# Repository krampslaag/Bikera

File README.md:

# Bikera
Turn bikes into IoT devices

What is Bikera? 
Bikera is a blockchain ecosystem that will function as a means to lend transportation and have it seamlessly maintained,
without having to worry about having a flat tire or any other mechanical difficulty that might cause inability to travel to your destination.

The Bikera network will always keep all the necessary parties informed on the latest and these will then swiftly present solutions. 
The means of transportation isn’t a solo challenge but a group effort. Depending on the class/group, roles will be assigned to accounts/persons. 
Acting on this role and delivering the requested solutions will result in a merit for these accounts/persons.

Accounts:
users would be comprised of classes/groups, each having a purpose to adding value to the ecosystem. Anyone can be in any or all of these groups. 

Consensus:
The ecosystem safeguarding will be done by the numbers of the masses and the randomness of travel-trajectory of these individuals,
this contributes to the Proof of Transit consensus protocol that will be used to mine the blocks.  
A layer2 solution will be used to track the bikes in movement; using LoraWAn nodes to verify the movement is real, 
this will route information to our own side blockchain, which will be used to fulfill contracts and token releases 
all our tokens will be created on this layer 2 or 1 blockchain for security reasons and immutability.  

Physical Assets:
Having real world assets used in a decentralized virtual system, needs a bridge between the virtual and the real world. 
This will be done by the development of a multi-functional lock. This lock will be implemented with a long-distance radio for receiving and transmitting data. 
There will also need to be storage to securely store private and public keys or other data. 
A GPS-module and/or Cellular network connectivity can be used to verify the location of the transportation, 
as feedback to the node network of gateway devices linking the lock to the blockchain. 

Wireless Communication: 
A network of radio receiving nodes need to be used or placed to receive data of these locks. 
Multiple nodes throughout a “two” dimensional space can be used to triangulate these locks and verify its location. 
The use-case of legacy or centralized networks can be used in the beginning and as verification of the decentralized network.

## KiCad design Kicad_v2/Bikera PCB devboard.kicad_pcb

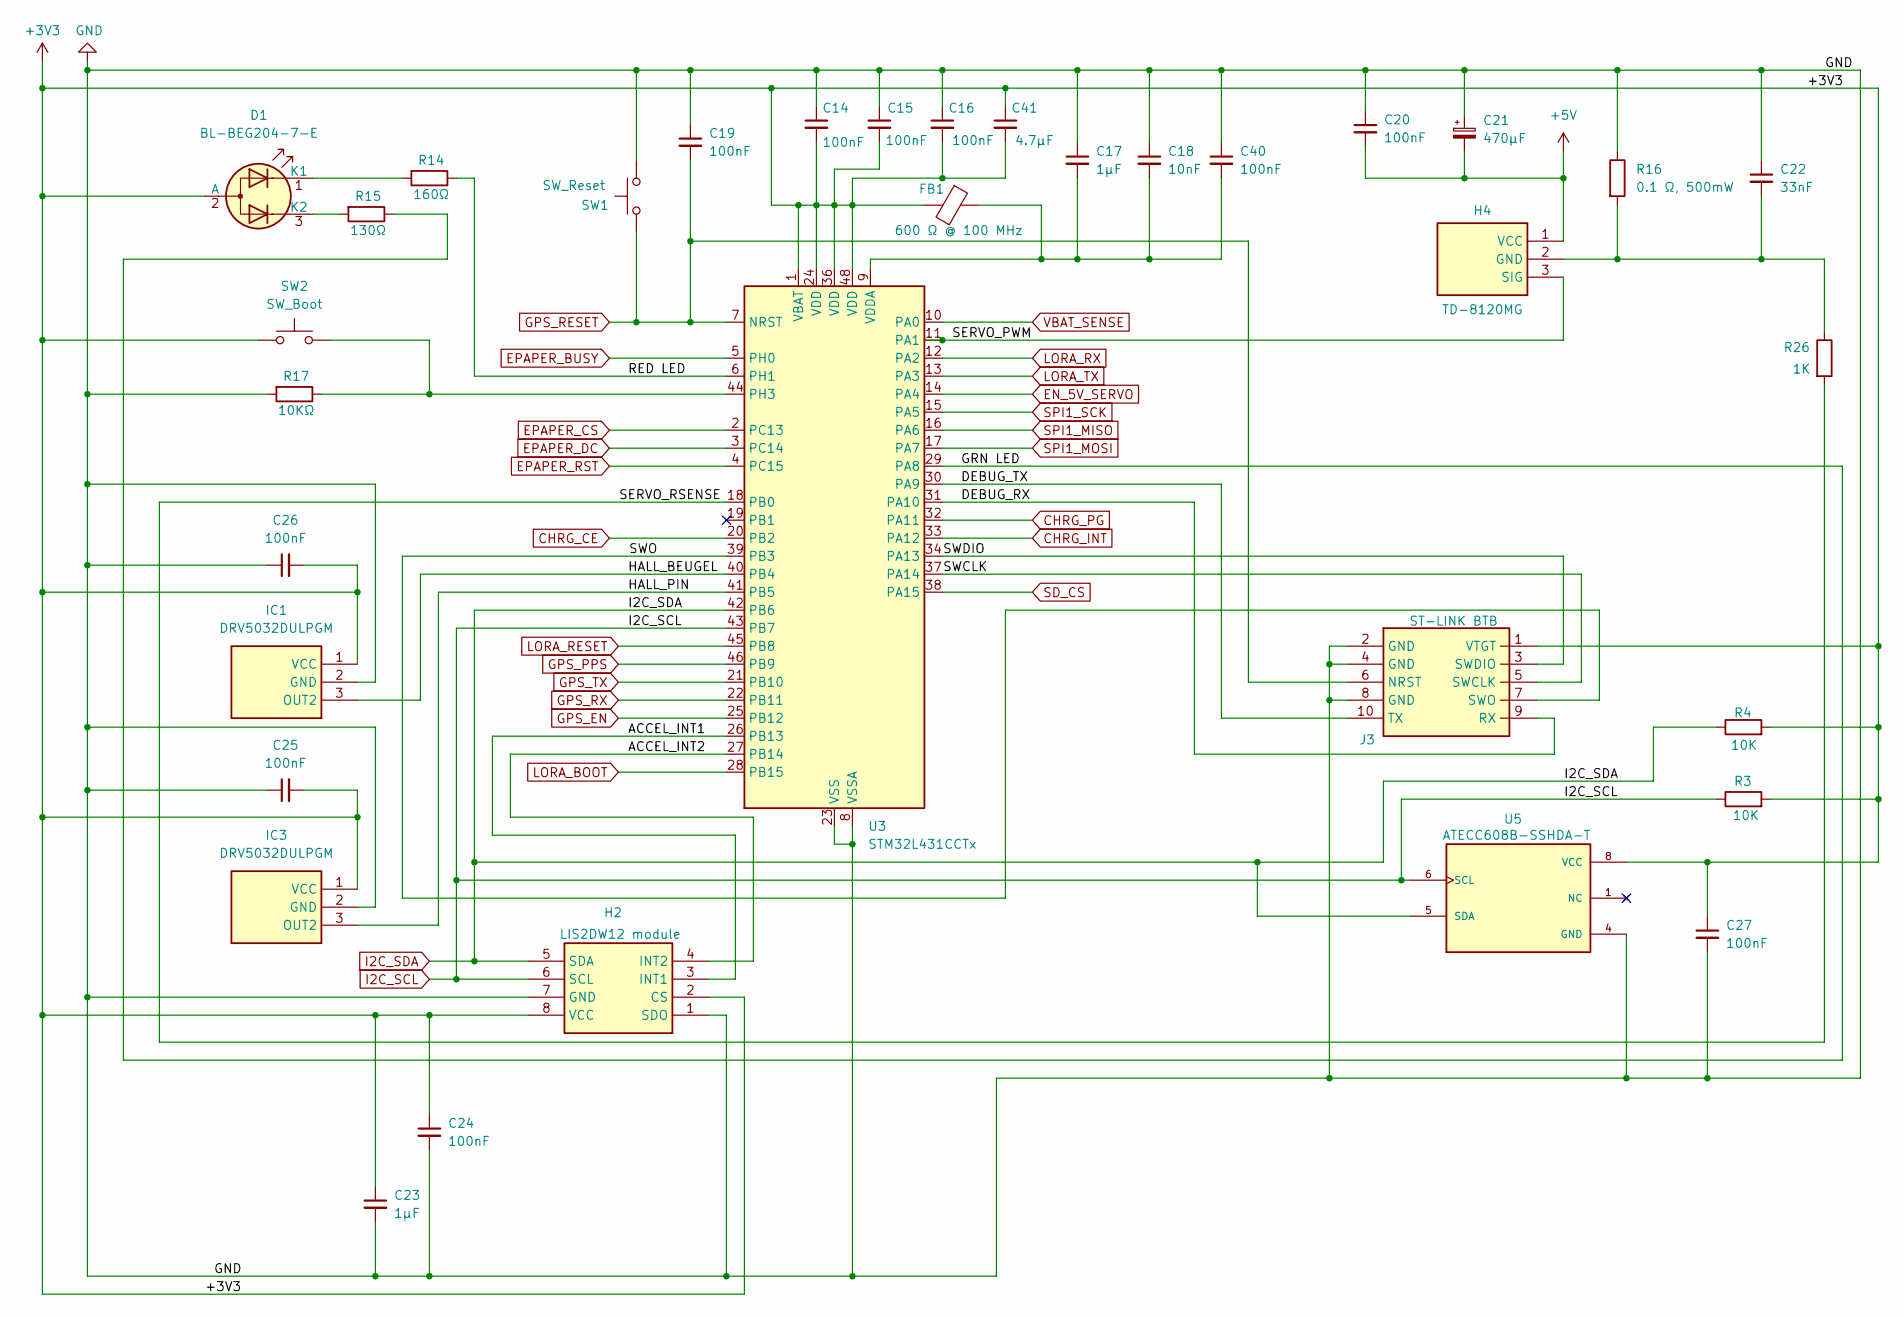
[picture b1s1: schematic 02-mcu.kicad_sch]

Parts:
C14, C15, C16, C19, C20, C24, C25, C26, C27, C40: 100nF; C_0603_1608Metric_Pad1.08x0.95mm_HandSolder
C17, C23: 1µF; C_0603_1608Metric_Pad1.08x0.95mm_HandSolder
C18: 10nF; C_0603_1608Metric_Pad1.08x0.95mm_HandSolder
C21: 470µF; CP_Radial_D8.0mm_P3.50mm
C22: 33nF; C_0603_1608Metric_Pad1.08x0.95mm_HandSolder
C41: 4.7µF; C_0603_1608Metric_Pad1.08x0.95mm_HandSolder
D1: BL-BEG204-7-E; LED_D5.0mm-3_Horizontal_O3.81mm_Z3.0mm
FB1: 600 Ω @ 100 MHz; L_0603_1608Metric_Pad1.05x0.95mm_HandSolder
H2: LIS2DW12 module; Mouser Part Number 727-FM24V01A-G
H4: TD-8120MG; JST_PH_B3B-PH-K_1x03_P2.00mm_Vertical; Mouser Part Number 595-DRV5032DULPGM
IC1, IC3: DRV5032DULPGM; Mouser Part Number 595-DRV5032DULPGM
J3: ST-LINK BTB; 009159010603906; Mouser Part Number 581-009159010603906
R3, R4: 10K; R_0603_1608Metric_Pad0.98x0.95mm_HandSolder
R14: 160Ω; R_0603_1608Metric_Pad0.98x0.95mm_HandSolder
R15: 130Ω; R_0603_1608Metric_Pad0.98x0.95mm_HandSolder
R16: 0.1 Ω, 500mW; R_1206_3216Metric_Pad1.30x1.75mm_HandSolder
R17: 10KΩ; R_0603_1608Metric_Pad0.98x0.95mm_HandSolder
R26: 1K; R_0603_1608Metric_Pad0.98x0.95mm_HandSolder
SW1: SW_Reset; SW_PUSH_6mm
SW2: SW_Boot; SW_PUSH_6mm
U3: STM32L431CCTx; LQFP-48_7x7mm_P0.5mm
U5: ATECC608B-SSHDA-T; DIP-8_W7.62mm_Socket; PARTREV B

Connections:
+3V3: C14.2, C15.2, C16.2, C23.1, C24.1, C25.2, C26.2, C27.1, C41.1, C41.2, D1.2 (A), FB1.2, H2.2 (CS), H2.8 (VCC), IC1.1 (VCC), IC3.1 (VCC), J3.1 (VTGT), R3.2, R4.2, SW2.1, U3.1 (VBAT), U3.24 (VDD), U3.36 (VDD), U3.48 (VDD), U5.8 (VCC); also elsewhere on the board
/MCU - Sensors - Actuators/ACCEL_INT1: H2.3 (INT1), U3.26 (PB13)
/MCU - Sensors - Actuators/ACCEL_INT2: H2.4 (INT2), U3.27 (PB14)
/MCU - Sensors - Actuators/DEBUG_RX: J3.9 (RX), U3.31 (PA10)
/MCU - Sensors - Actuators/DEBUG_TX: J3.10 (TX), U3.30 (PA9)
/MCU - Sensors - Actuators/GRN LED: R15.1, U3.29 (PA8)
/MCU - Sensors - Actuators/HALL_BEUGEL: IC1.3 (OUT2), U3.40 (PB4)
/MCU - Sensors - Actuators/HALL_PIN: IC3.3 (OUT2), U3.41 (PB5)
/MCU - Sensors - Actuators/RED LED: R14.1, U3.6 (PH1)
/MCU - Sensors - Actuators/SERVO_PWM: H4.3 (SIG), U3.11 (PA1)
/MCU - Sensors - Actuators/SERVO_RSENSE: R26.2, U3.18 (PB0)
/MCU - Sensors - Actuators/SWCLK: J3.5 (SWCLK), U3.37 (PA14)
/MCU - Sensors - Actuators/SWDIO: J3.3 (SWDIO), U3.34 (PA13)
/MCU - Sensors - Actuators/SWO: J3.7 (SWO), U3.39 (PB3)
CHRG_CE: U3.20 (PB2); also elsewhere on the board
CHRG_INT: U3.33 (PA12); also elsewhere on the board
CHRG_PG: U3.32 (PA11); also elsewhere on the board
EN_5V_SERVO: U3.14 (PA4); also elsewhere on the board
EPAPER_BUSY: U3.5 (PH0); also elsewhere on the board
EPAPER_CS: U3.2 (PC13); also elsewhere on the board
EPAPER_DC: U3.3 (PC14); also elsewhere on the board
EPAPER_RST: U3.4 (PC15); also elsewhere on the board
GND: C14.1, C15.1, C16.1, C17.1, C18.1, C19.1, C20.1, C21.1, C22.1, C23.2, C24.2, C25.1, C26.1, C27.2, C40.1, H2.1 (SDO), H2.7 (GND), IC1.2 (GND), IC3.2 (GND), J3.2 (GND), J3.4 (GND), J3.8 (GND), R16.1, R17.2, SW1.2, U3.8 (VSSA), U3.23 (VSS), U3.35 (VSS), U3.47 (VSS), U5.4 (GND); also elsewhere on the board
GPS_EN: U3.25 (PB12); also elsewhere on the board
GPS_PPS: U3.46 (PB9); also elsewhere on the board
GPS_RESET: C19.2, J3.6 (NRST), SW1.1, U3.7 (NRST); also elsewhere on the board
GPS_RX: U3.22 (PB11); also elsewhere on the board
GPS_TX: U3.21 (PB10); also elsewhere on the board
I2C_SCL: H2.6 (SCL), R3.1, U3.43 (PB7), U5.6 (SCL); also elsewhere on the board
I2C_SDA: H2.5 (SDA), R4.1, U3.42 (PB6), U5.5 (SDA); also elsewhere on the board
LORA_BOOT: U3.28 (PB15); also elsewhere on the board
LORA_RESET: U3.45 (PB8); also elsewhere on the board
LORA_RX: U3.12 (PA2); also elsewhere on the board
LORA_TX: U3.13 (PA3); also elsewhere on the board
unnamed: D1.1 (K1), R14.2
unnamed: D1.3 (K2), R15.2
unnamed: C22.2, H4.2 (GND), R16.2, R26.1
unnamed: R17.1, SW2.2, U3.44 (PH3)
unnamed: C17.2, C18.2, C40.2, FB1.1, U3.9 (VDDA)
SD_CS: U3.38 (PA15); also elsewhere on the board
SPI1_MISO: U3.16 (PA6); also elsewhere on the board
SPI1_MOSI: U3.17 (PA7); also elsewhere on the board
SPI1_SCK: U3.15 (PA5); also elsewhere on the board
VBAT_SENSE: U3.10 (PA0); also elsewhere on the board

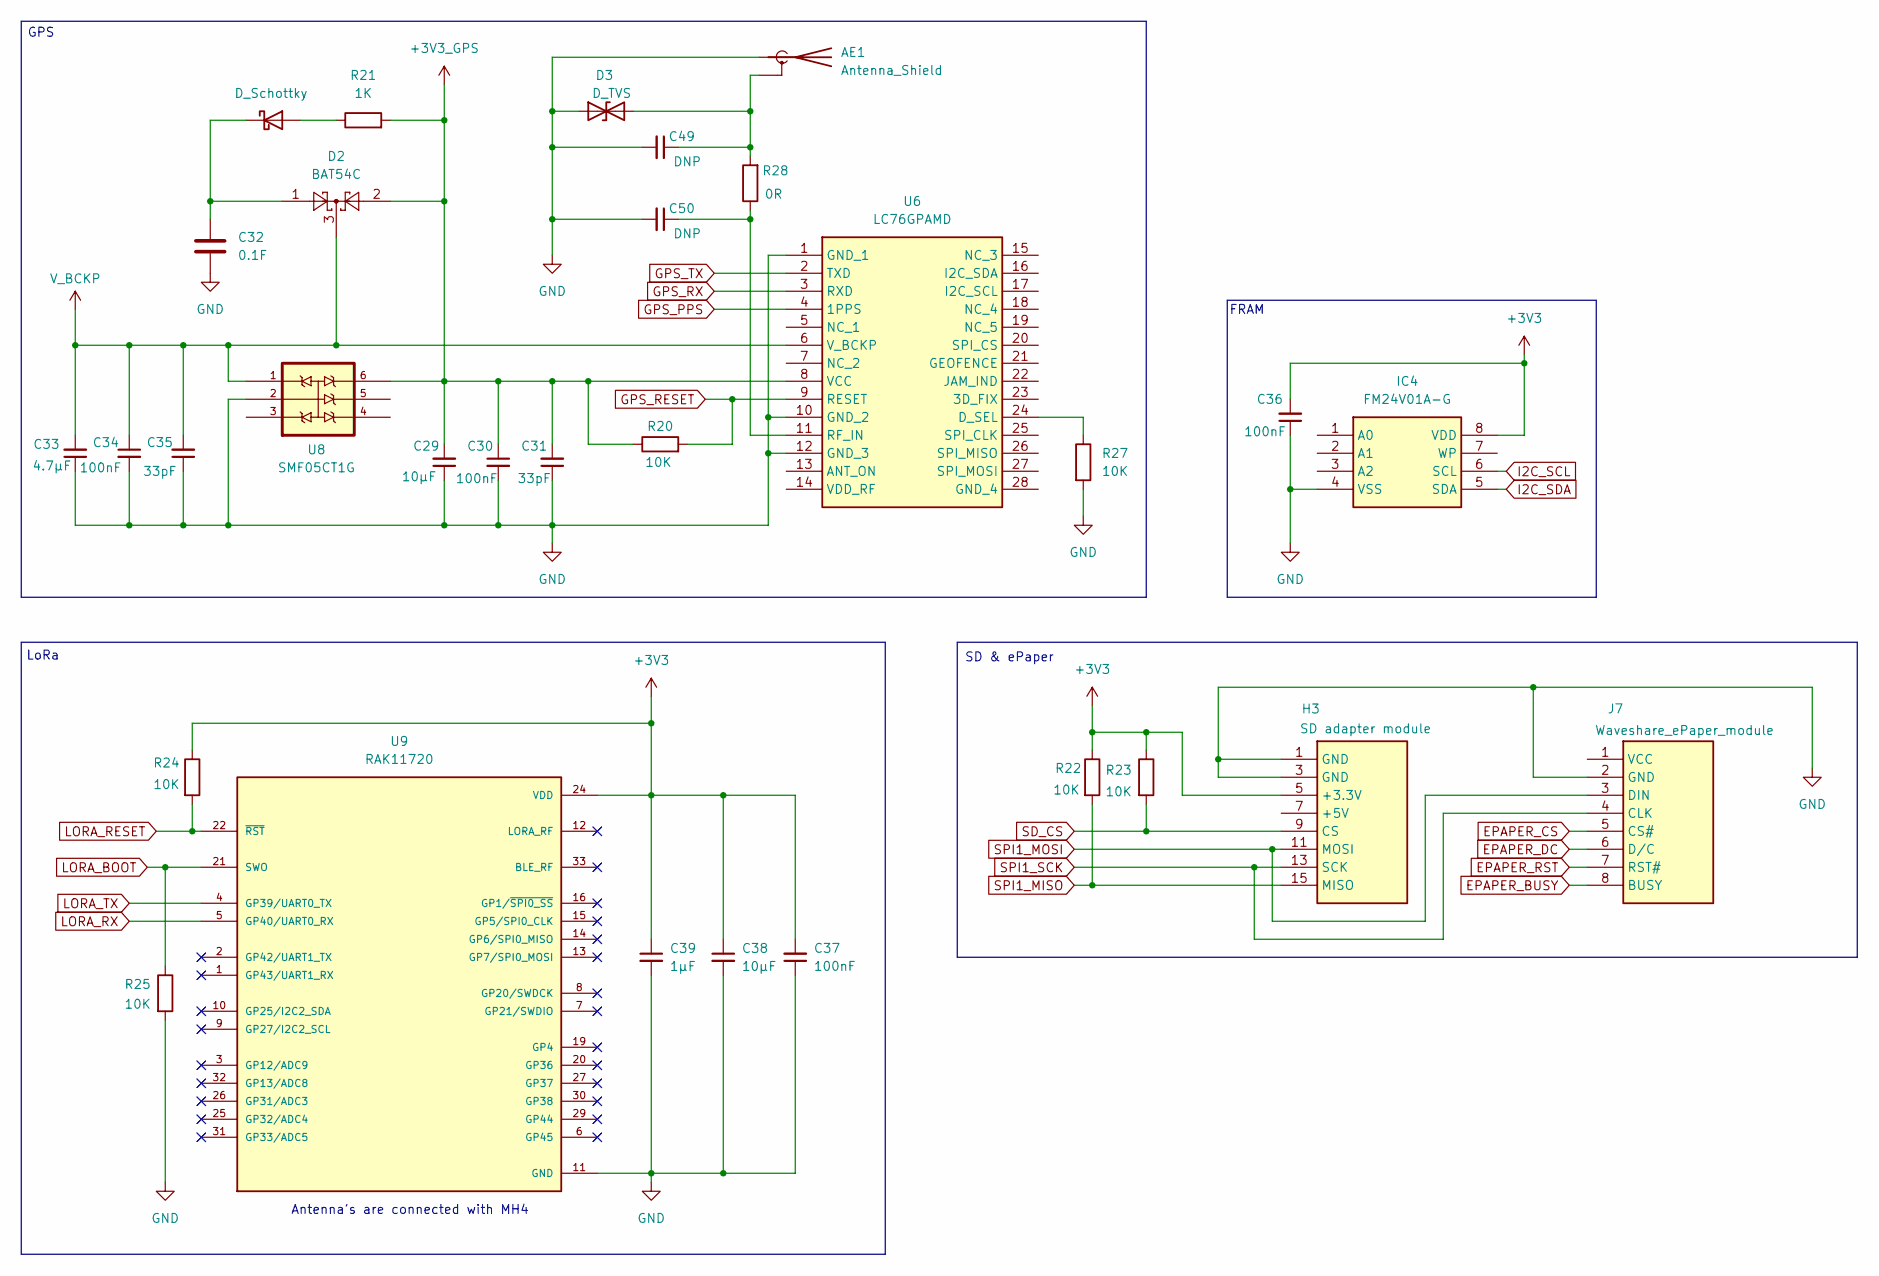
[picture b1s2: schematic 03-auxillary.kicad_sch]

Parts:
AE1: Antenna_Shield; U.FL_Hirose_U.FL-R-SMT-1_Vertical
C29, C38: 10µF; C_0603_1608Metric_Pad1.08x0.95mm_HandSolder
C30, C34, C36, C37: 100nF; C_0603_1608Metric_Pad1.08x0.95mm_HandSolder
C31, C35: 33pF; C_0603_1608Metric_Pad1.08x0.95mm_HandSolder
C32: 0.1F; C_1210_3225Metric_Pad1.33x2.70mm_HandSolder
C33: 4.7µF; C_0603_1608Metric_Pad1.08x0.95mm_HandSolder
C39: 1µF; C_0603_1608Metric_Pad1.08x0.95mm_HandSolder
C49, C50: DNP; C_0402_1005Metric_Pad0.74x0.62mm_HandSolder
D2: BAT54C; SOT-23_Handsoldering
D3: D_TVS; D_SOD-923
D4: D_Schottky; D_SOD-523
H3: SD adapter module; PinHeader_2x08_P2.54mm_Vertical
IC4: FM24V01A-G; SOIC127P602X173-8N; Mouser Part Number 727-FM24V01A-G
J7: Waveshare_ePaper_module; JST_PH_B8B-PH-K_1x08_P2.00mm_Vertical
R20, R22, R23, R24, R25, R27: 10K; R_0603_1608Metric_Pad0.98x0.95mm_HandSolder
R21: 1K; R_0603_1608Metric_Pad0.98x0.95mm_HandSolder
R28: 0R; R_0402_1005Metric_Pad0.72x0.64mm_HandSolder
U6: LC76GPAMD; Mouser Part Number 277-LC76GPAMD
U8: SMF05CT1G; SOT65P210X110-6N
U9: RAK11720; XCVR_RAK11720; PARTREV 6/2/2023

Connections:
+3V3: C36.2, C37.2, C38.1, C39.1, H3.5 (+3.3V), H3.6 (+3.3V), IC4.8 (VDD), R22.1, R23.1, R24.1, U9.24 (VDD); also elsewhere on the board
+3V3_GPS: C29.2, C30.1, C31.2, D2.2, R20.1, R21.2, U6.8 (VCC), U8.6; also elsewhere on the board
EPAPER_BUSY: J7.8 (BUSY); also elsewhere on the board
EPAPER_CS: J7.5 (CS#); also elsewhere on the board
EPAPER_DC: J7.6 (D/C); also elsewhere on the board
EPAPER_RST: J7.7 (RST#); also elsewhere on the board
GND: AE1.1 (A), C29.1, C30.2, C31.1, C32.2, C33.1, C34.2, C35.1, C36.1, C37.1, C38.2, C39.2, C49.2, C50.2, D3.1 (A1), H3.1 (GND), H3.2 (GND), H3.3 (GND), H3.4 (GND), IC4.4 (VSS), J7.2 (GND), R25.2, R27.2, U6.1 (GND_1), U6.10 (GND_2), U6.12 (GND_3), U8.2, U9.11 (GND), U9.17 (GND), U9.18 (GND), U9.23 (GND), U9.28 (GND), U9.34 (GND); also elsewhere on the board
GPS_PPS: U6.4 (1PPS); also elsewhere on the board
GPS_RESET: R20.2, U6.9 (RESET); also elsewhere on the board
GPS_RX: U6.3 (RXD); also elsewhere on the board
GPS_TX: U6.2 (TXD); also elsewhere on the board
I2C_SCL: IC4.6 (SCL); also elsewhere on the board
I2C_SDA: IC4.5 (SDA); also elsewhere on the board
LORA_BOOT: R25.1, U9.21 (SWO); also elsewhere on the board
LORA_RESET: R24.2, U9.22 (~RST); also elsewhere on the board
LORA_RX: U9.5 (GP40/UART0_RX); also elsewhere on the board
LORA_TX: U9.4 (GP39/UART0_TX); also elsewhere on the board
unnamed: AE1.2 (Shield), C49.1, D3.2 (A2), R28.2
unnamed: D4.2 (A), R21.1
unnamed: C32.1, D2.1, D4.1 (K)
unnamed: R27.1, U6.24 (D_SEL)
unnamed: C50.1, R28.1, U6.11 (RF_IN)
SD_CS: H3.9 (CS), H3.10 (CS), R23.2; also elsewhere on the board
SPI1_MISO: H3.15 (MISO), H3.16 (MISO), R22.2; also elsewhere on the board
SPI1_MOSI: H3.11 (MOSI), H3.12 (MOSI), J7.3 (DIN); also elsewhere on the board
SPI1_SCK: H3.13 (SCK), H3.14 (SCK), J7.4 (CLK); also elsewhere on the board
V_BCKP: C33.2, C34.1, C35.2, D2.3, U6.6 (V_BCKP), U8.1

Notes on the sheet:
Antenna's are connected with MH4
LoRa
SD & ePaper
GPS
FRAM

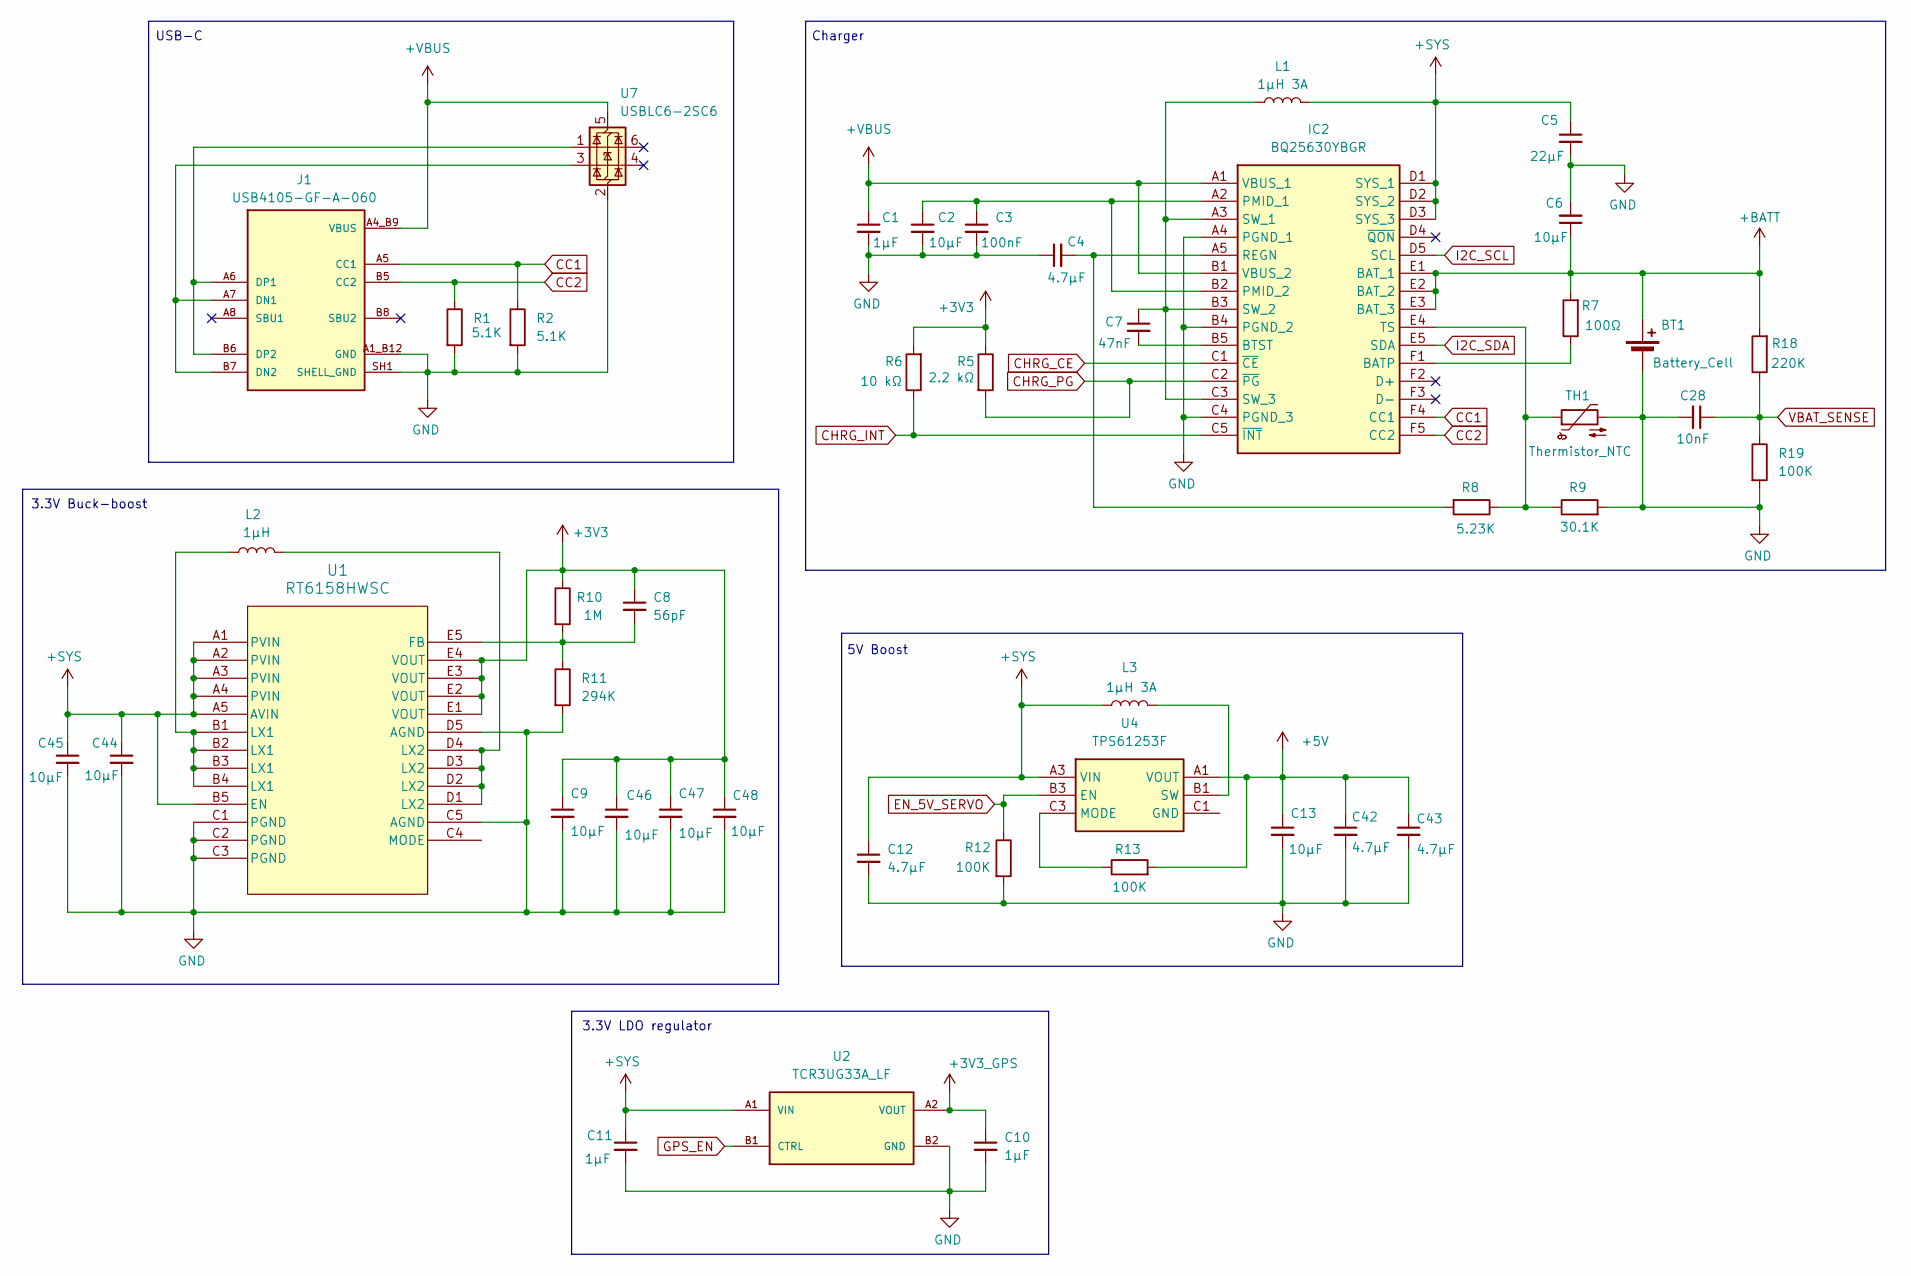
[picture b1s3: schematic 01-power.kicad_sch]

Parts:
BT1: Battery_Cell; JST_PH_S2B-PH-K_1x02_P2.00mm_Horizontal
C1, C10, C11: 1µF; C_0603_1608Metric_Pad1.08x0.95mm_HandSolder
C2, C6, C9, C13, C44, C45, C46, C47, C48: 10µF; C_0603_1608Metric_Pad1.08x0.95mm_HandSolder
C3: 100nF; C_0603_1608Metric_Pad1.08x0.95mm_HandSolder
C4, C12, C42, C43: 4.7µF; C_0603_1608Metric_Pad1.08x0.95mm_HandSolder
C5: 22µF; C_0805_2012Metric_Pad1.18x1.45mm_HandSolder
C7: 47nF; C_0603_1608Metric_Pad1.08x0.95mm_HandSolder
C8: 56pF; C_0603_1608Metric_Pad1.08x0.95mm_HandSolder
C28: 10nF; C_0603_1608Metric_Pad1.08x0.95mm_HandSolder
IC2: BQ25630YBGR; BGA30C40P5X6_221X271X50; Manufacturer_Part_Number BQ25630YBGR
J1: USB4105-GF-A-060; USB_C_Receptacle_GCT_USB4105-xx-A_16P_TopMnt_Horizontal
L1, L3: 1µH 3A; MAKK2520H1R0M
L2: 1µH; MAKK2520H1R0M
R1, R2: 5.1K; R_0603_1608Metric_Pad0.98x0.95mm_HandSolder
R5: 2.2 kΩ; R_0603_1608Metric_Pad0.98x0.95mm_HandSolder
R6: 10 kΩ; R_0603_1608Metric_Pad0.98x0.95mm_HandSolder
R7: 100Ω; R_0603_1608Metric_Pad0.98x0.95mm_HandSolder
R8: 5.23K; R_0603_1608Metric_Pad0.98x0.95mm_HandSolder
R9: 30.1K; R_0603_1608Metric_Pad0.98x0.95mm_HandSolder
R10: 1M; R_0402_1005Metric
R11: 294K; R_0402_1005Metric
R12, R13, R19: 100K; R_0603_1608Metric_Pad0.98x0.95mm_HandSolder
R18: 220K; R_0603_1608Metric_Pad0.98x0.95mm_HandSolder
TH1: Thermistor_NTC; C_Disc_D3.4mm_W2.1mm_P2.50mm
U1: RT6158HWSC; BGA25_RT6158H_RIT-M
U2: TCR3UG33A_LF; BGA4N35P2X2_64X64X33; PARTREV 2021-10-28
U4: TPS61253F; BGA9N40P3X3_119X128X62N; Mouser Part Number 727-FM24V01A-G
U7: USBLC6-2SC6; SOT-23-6_Handsoldering

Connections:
+3V3: C8.1, C9.1, C46.1, C47.1, C48.1, R5.1, R6.2, R10.1, U1.E1 (VOUT), U1.E2 (VOUT), U1.E3 (VOUT), U1.E4 (VOUT); also elsewhere on the board
+3V3_GPS: C10.1, U2.A2 (VOUT); also elsewhere on the board
+BATT: BT1.1 (+), C6.1, IC2.E1 (BAT_1), IC2.E2 (BAT_2), IC2.E3 (BAT_3), R7.2, R18.2
+SYS: C5.1, C11.1, C12.1, C44.1, C45.1, IC2.D1 (SYS_1), IC2.D2 (SYS_2), IC2.D3 (SYS_3), L1.2, L3.1, U1.A1 (PVIN), U1.A2 (PVIN), U1.A3 (PVIN), U1.A4 (PVIN), U1.A5 (AVIN), U1.B5 (EN), U2.A1 (VIN), U4.A3 (VIN)
+VBUS: C1.1, IC2.A1 (VBUS_1), IC2.B1 (VBUS_2), J1.A4_B9 (VBUS), J1.B4_A9 (VBUS), U7.5 (VBUS)
CC1: IC2.F4 (CC1), J1.A5 (CC1), R2.1
CC2: IC2.F5 (CC2), J1.B5 (CC2), R1.1
CHRG_CE: IC2.C1 (~CE); also elsewhere on the board
CHRG_INT: IC2.C5 (~INT), R6.1; also elsewhere on the board
CHRG_PG: IC2.C2 (~PG), R5.2; also elsewhere on the board
EN_5V_SERVO: R12.1, U4.B3 (EN); also elsewhere on the board
GND: BT1.2 (-), C1.2, C2.2, C3.2, C4.1, C5.2, C6.2, C9.2, C10.2, C11.2, C12.2, C13.2, C28.2, C42.2, C43.2, C44.2, C45.2, C46.2, C47.2, C48.2, IC2.A4 (PGND_1), IC2.B4 (PGND_2), IC2.C4 (PGND_3), J1.A1_B12 (GND), J1.B1_A12 (GND), J1.SH1 (SHELL_GND), J1.SH2 (SHELL_GND), J1.SH3 (SHELL_GND), J1.SH4 (SHELL_GND), R1.2, R2.2, R9.2, R11.2, R12.2, R19.2, TH1.2, U1.C1 (PGND), U1.C2 (PGND), U1.C3 (PGND), U1.C5 (AGND), U1.D5 (AGND), U2.B2 (GND), U7.2 (GND); also elsewhere on the board
GPS_EN: U2.B1 (CTRL); also elsewhere on the board
I2C_SCL: IC2.D5 (SCL); also elsewhere on the board
I2C_SDA: IC2.E5 (SDA); also elsewhere on the board
unnamed: IC2.F1 (BATP), R7.1
unnamed: C7.2, IC2.B5 (BTST)
unnamed: C2.1, C3.1, IC2.A2 (PMID_1), IC2.B2 (PMID_2)
unnamed: C4.2, IC2.A5 (REGN), R8.2
unnamed: C7.1, IC2.A3 (SW_1), IC2.B3 (SW_2), IC2.C3 (SW_3), L1.1
unnamed: IC2.E4 (TS), R8.1, R9.1, TH1.1
unnamed: J1.A7 (DN1), J1.B7 (DN2), U7.3 (I/O2)
unnamed: J1.A6 (DP1), J1.B6 (DP2), U7.1 (I/O1)
unnamed: L2.1, U1.B1 (LX1), U1.B2 (LX1), U1.B3 (LX1), U1.B4 (LX1)
unnamed: L2.2, U1.D1 (LX2), U1.D2 (LX2), U1.D3 (LX2), U1.D4 (LX2)
unnamed: L3.2, U4.B1 (SW), U4.B2 (SW)
unnamed: C8.2, R10.2, R11.1, U1.E5 (FB)
unnamed: U4.C1 (GND), U4.C2 (GND)
unnamed: R13.1, U4.C3 (MODE)
VBAT_SENSE: C28.1, R18.1, R19.1; also elsewhere on the board

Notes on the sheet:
3.3V Buck-boost
USB-C
3.3V LDO regulator
5V Boost
Charger

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
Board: 4 copper layers, 114 parts (48 on the bottom side), 71 nets, no tracks yet.

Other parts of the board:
H10, H11, H12, H13: MountingHole_3.2mm_M3_Pad

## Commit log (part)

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2023-08-08 white paper for the Bikera Network
2023-08-08 MERA logo
2023-08-08 Create README.md
    Short description of the Bikera network
2023-08-08 The whitepaper for the Bikera network
2024-02-25 bikera v2.1
    smart contract for audit purposess
2024-02-25 Bikera Smart contract V1
    audit purposes, old version contract
2024-02-25 version 2.1
    finalised version for token launch, tested on sepolia network
    see on sepolia etherscan
    contract adress:
    0x25EE85C5E86293C8Ba874A505F4C5D21c19231F9
2024-03-08 new logo for Bikera MERA
2024-03-08 Deployed contract on Ethereum
2024-10-03 mkdir my-new-folder
2024-10-04 Update Helium_integration_v0.0.1.json
    trying to get array input HEX as array output HEX, so that in further programs the conversion is in INT of HEX format. this to save data on blockchain, find out which data size runs natively and fast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
2024-10-04 Update Helium_integration_v0.0.1.json
    got HEX output, INT output and String output, compatibility arr.
2024-10-04 Update Helium_integration_v0.0.1.json
    HEX (16) Integer (10) !! Base64 needs or can be added if necessary.
2024-10-07 Update MKRWAN_PAYLOAD_CUSTOM_BIKERA.ino
    Trying to get it functioning with the Wio module for gps coordinates.
2024-10-07 Update and rename Helium_integration_v0.0.1.json to Helium_integration_v0.0.1.js
    Is written in javascript. Not sure if json or nodjs extension should be required. Get Helium CLI and find out!
2024-10-14 Update MKRWAN_PAYLOAD_CUSTOM_BIKERA.ino
    big lines of draft of draft of draft of draft of DRAFT
2024-10-15 Update MKRWAN_PAYLOAD_CUSTOM_BIKERA.ino
    starting connection en setting up lock partially structure line-out
2024-10-15 Update MKRWAN_PAYLOAD_CUSTOM_BIKERA.ino
    workloads, private key generation or input added. And device check by calculating public key
2024-10-16 Update MKRWAN_PAYLOAD_CUSTOM_BIKERA.ino
    Crypto chip setup part, input private key (have a copy of the wallet address in case the chip dies or the lock gets destroyed the funds are still accessible by generating a mobile wallet with the key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
2024-10-16 Update MKRWAN_PAYLOAD_CUSTOM_BIKERA.ino
    some notably interesting info on how to use the ECC608 crypto key and future imlpications of the network
2024-10-18 Update MKRWAN_PAYLOAD_CUSTOM_BIKERA.ino
    LFG for this iteration, now just make the arduino send random numbers that should be locked as coordinates with assigned Public key encryption.
2024-10-20 Update MKRWAN_PAYLOAD_CUSTOM_BIKERA.ino
    Setup, entering stuff, probably should write this to EEPROM; in case somebody just start cracking open the locks and replaces SD-cards with malicious ones, depends on if the price of an SD card is wo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
2024-10-21 Update MKRWAN_PAYLOAD_CUSTOM_BIKERA.ino
    Let's try to compile this Gaint Bug of code
2024-10-21 Update MKRWAN_PAYLOAD_CUSTOM_BIKERA.ino
    Debuugggiiiinnnngggg
2024-10-23 Update MKRWAN_PAYLOAD_CUSTOM_BIKERA.ino
    debugged and compiles.
    let's take this for a testdrive. Next is head-on with the configuration file. this is now set to TLS but it is not completely similar on which slots to lock and which to use for this application
2024-10-23 Update MKRWAN_PAYLOAD_CUSTOM_BIKERA.ino
    Fixing bugs
2024-10-24 Update MKRWAN_PAYLOAD_CUSTOM_BIKERA.ino
    getting the setup to run, serial monitor conversion needs to be looked at. trying other desktop environment maybe this is due to Debian12 and the UART interface. let's see If this isn't a problem on 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
2024-10-25 Update MKRWAN_PAYLOAD_CUSTOM_BIKERA.ino
    flashstorage problems with strings.
2024-10-25 Rename MKRWAN_PAYLOAD_CUSTOM_BIKERA.ino to MKRWAN_PAYLOAD_CUSTOM_BIKERA_MKRWAN1310.ino
    this is the MKRWAN firmware prototype, later in development the Arduino NANO ble 33 IOT will also be used and after setting these two type boards up to run firmware for Bikera network ESP32 will be t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
2024-10-25 Update MKRWAN_PAYLOAD_CUSTOM_BIKERA_MKRWAN1310.ino
    trying to get the serial input to read bytes as hexadecimal format
2025-01-21 Create test file to create folder
2025-01-21 Create test
2025-07-02 Create PotBotBlock_Telegram
2025-08-14 telegram bot replit version
2025-08-14 Remove nested repository and add to gitignore
2025-08-15 Your commit message
2025-08-15 update 15082025e
2025-08-15 20250815d
2025-08-20 front end webpage online added correctly twice
2025-08-20 front end webpage added services
2025-08-23 Add Backend Components
2025-08-24 Powerpoint presentation
2025-08-25 Powerpoint presentation v2
2025-08-28 rust implementation of canisters on ICP
2025-08-28 rust implementation of canisters on ICP compartementalize
2025-08-28 Remove node_modules and add to gitignore
2025-08-28 Add dfx files to gitignore
2025-08-28 Add compressor and wrangler config
2025-08-31 got canisters working locally
2025-08-31 Remove build artifacts from version control
2025-08-31 Add .gitignore to exclude build artifacts
2025-08-31 cleaned up version
2025-08-31 failed copy paste
2025-08-31 getting te canisters to function in sync and get it running on mainnet ICP
2025-08-31 supabase and worker.js update monster, need XP canister stil debug and go
2025-08-31 final update today, XP token added and the API routes that need refining to link front to back
2025-09-07 added API routing and correcting variable naming
2025-09-14 architectural format of the canisters
2025-09-14 cleaning up a littles
2025-09-21 getting ready for regulations
2025-10-07 user database for ICP
2026-02-04 Document voor componenten, STM32L0, L1 en L4 vergeleken
2026-02-05 STM32 prijzen en voorstel
2026-02-05 STM32WL?
2026-02-06 LoRa
2026-02-11 LoRa antennes
2026-02-22 ECC chip: ATECC608B
2026-02-23 Draadantenne
2026-02-28 BLE antenne
2026-03-01 ECC update
2026-03-02 GPS u-blox
2026-03-03 GPS Quectel
2026-03-06 E-ink
2026-03-10 Accelerometer
2026-03-11 Readme
2026-03-16 Architectuur schema begin
2026-03-19 Architectuur schema
2026-03-20 Architectuurschema Lora, GPS, ePaper
2026-03-24 BMS lader en USB stromen
2026-03-26 BMS converters
2026-03-27 BMS 5V boost
2026-03-27 Inhoudstafel
2026-03-31 5V boost
2026-04-01 5V boost en accelerometer
2026-04-19 Kleurled en hall effect sensor
2026-04-21 Architectuurschema FRAM en accelerometer
2026-04-22 Architectuurschema BMS
2026-04-25 Architectuur schema structuur
2026-04-28 LED, GPS antenne
2026-04-29 Architectuurschema LED en GPS antenne
2026-04-29 Componenten bijgewerkt en architectuurschema hall sensors
2026-05-02 ST-link
2026-05-06 KiCad project aangemaakt
2026-05-06 untrack .history
2026-05-07 untrack backups
2026-05-07 KiCad symbolen geïmporteerd
2026-05-08 Readme makeover - stand van zaken
2026-05-08 Readme update
2026-05-12 KiCad symbolen basiscomponenten
2026-05-14 3.3V buck-boost: RT6150B
2026-05-16 schema design KiCAD layout guide
2026-05-16 KiCAD generated pages
    dit zijn autogenerated pages, dienen nog leesbaar gemaakt te worden
2026-05-16 schema uitwerkingsgids
    beschrijving van hoe de belegging is per pagina
2026-05-16 3.3V buck-boost veranderd: RT6158AWSC
2026-05-16 Drawio HTML export
2026-05-17 Architectuurschema BMS en SD bijgewerkt
2026-05-28 Kleine update
2026-06-11 gitignore
2026-06-22 Schema van Eli
2026-06-25 Add Kicad_v2 folder (devboard + prototype schematics, libraries)
2026-06-29 KiCad MCU schema gecontroleerd
